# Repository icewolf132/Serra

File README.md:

<div align="center">

# Serra automatizzata

### Sistema embedded per il controllo di una serra con microcontrollori Microchip PIC

*Un progetto pratico che integra firmware per microcontrollori, progettazione elettronica e controllo di sensori e attuatori.*

</div>

---

## Panoramica

Questa **serra automatizzata** è un progetto embedded sviluppato per riprodurre, su scala prototipale, alcuni elementi di un sistema di controllo per una serra industriale. Il sistema combina due microcontrollori **Microchip PIC16F887 e PIC16F88**, schede elettroniche progettate e realizzate appositamente, sensori di temperatura e attuatori per la ventilazione e il movimento dell'asta d'irrigazione.

Il progetto comprende sia la parte software — firmware dei microcontrollori — sia la parte hardware: schemi elettrici, progettazione delle PCB e integrazione dei componenti. Il repository raccoglie il materiale tecnico disponibile e offre una base per documentare il funzionamento del sistema e le successive evoluzioni.

> **Stato del progetto:** il sistema di base è stato realizzato. È in progetto un'evoluzione con funzionalità IoT e soluzioni di comunicazione più strutturate. Le funzionalità future sono indicate come tali e non come già implementate.

## Galleria del progetto

> **Aggiungi le fotografie reali del progetto** nella cartella `documentazione/immagini/`, usando i nomi indicati qui sotto. Le immagini verranno visualizzate direttamente nella pagina GitHub. Sono particolarmente utili una foto della serra completa, una foto per ciascuna PCB e un'immagine del layout in KiCad.

<div align="center">
  
  <p><em>Vista complessiva del prototipo</em></p>
</div>

<table>
  <tr>
    <td width="50%" align="center">
      
      <br/><em>Panello di controllo</em>
    </td>
    <td width="50%" align="center">
      
      <br/><em>Scheda per il controllo del motore</em>
    </td>
  </tr>
  <tr>
    <td colspan="2" align="center">
      
      <br/><em>Progettazione elettronica in KiCad</em>
    </td>
  </tr>
</table>

## Funzionalità e componenti

Il prototipo comprende i seguenti elementi, realizzati o integrati nel sistema:

| Sistema | Componenti |
|---|---|
| Panello di controllo | Microcontrollore Microchip **PIC16F887** |
| Driver motore |  **PIC16F88** e  il ponte h **L298N** |
| Sensore di temperatura | Sensore analogico **LM35** |
| Ventilazione | Ventola comandata dal panello di controllo|
| Apertura delle finestre | Relè utilizzati per comandare il meccanismo di apertura |
| Movimento della barra d'irrigazione | **Motore DC da 12V** con **Encoder**, gestito dal driver motore |
| Hardware custom | Schede **PCB** progettate e realizzate personalmente (compresa la fotoincincisione)|

I maggiori dettagli riguardo i sensori e degli altri componenti possono essere consultati negli schemi elettrici e nei datasheet presenti nel repository.

## Architettura del sistema

Il sistema adotta una struttura composta da un controllore principale e da una scheda periferica dedicata al motore. I due PIC non utilizzano un protocollo seriale standard per comunicare: lo scambio di comandi avviene tramite **semplici segnali digitali**, interpretati come livello logico alto o basso.

<div align="center">
  
</div>

*Il diagramma è una rappresentazione concettuale dell'architettura descritta. Per i collegamenti elettrici dettagliati fanno fede gli schemi del progetto.*

### Schede elettroniche e PCB

La parte hardware è stata progettata e realizzata nell'ambito del progetto, non assemblata esclusivamente usando moduli già pronti. Il repository include i materiali di progettazione elettronica sviluppati con **KiCad**.

La documentazione hardware è utile per:

- consultare gli schemi elettrici;
- esaminare il layout delle PCB;
- identificare i componenti e i relativi collegamenti;
- comprendere la separazione tra controllore principale e scheda periferica.

Quando possibile, è consigliato affiancare ai file sorgente di KiCad anche esportazioni PDF degli schemi, immagini del layout e fotografie delle schede fisiche assemblate.

## Firmware

Il firmware è organizzato in base al ruolo dei due microcontrollori:

- **Controllore principale — PIC16F887:** gestisce la logica centrale del sistema e interagisce con i sensori e gli attuatori previsti dall'architettura.
- **Controllore periferico — PIC16F88:** è dedicato al controllo del motore DC da 12 V tramite il ponte h **L298N** e riceve comandi dal controllore principale tramite segnali digitali.

I sorgenti sono disponibili nella cartella [`firmware/`](firmware/). Le istruzioni di compilazione e programmazione devono fare riferimento ai file di progetto e alla toolchain effettivamente utilizzata per il firmware, nonché **MPLAB IDE v6.20**.

> **Nota sulla comunicazione:** il collegamento tra i due microcontrollori è realizzato tramite livelli logici digitali. Non è implementato, nella versione descritta, un protocollo come UART, SPI o I²C.

## Struttura del repository

```text
Serra/
├── README.md
├── Firmware/          # Sorgenti dei firmware
├── Schemi/            # Schemi elettrici e progetti PCB (KiCad)
└── Documentazione/    # Relazione tecnica, datasheet e materiali di supporto
```

Questa è la struttura logica del progetto: alcuni nomi o sottopercorsi possono variare in base all'organizzazione effettiva dei file nel repository.

## Documentazione tecnica

Nel repository sono raccolti diversi tipi di materiale tecnico:

- **Relazione tecnica PDF:** descrizione formale del progetto, delle scelte progettuali e dei problemi riscontrati. 
- **Schemi e PCB KiCad:** sorgenti editabili della progettazione elettronica.
- **Datasheet:** documentazione dei produttori per consultare caratteristiche elettriche, pinout, limiti operativi e modalità d'impiego dei componenti.
- **Firmware:** codice dei microcontrollori impiegati nel prototipo.

Per facilitare la consultazione, è consigliato mantenere i datasheet raggruppati in una cartella dedicata e creare un piccolo indice con **sigla del componente**, **funzione nel progetto** e **nome del relativo PDF**.

## Sviluppi futuri

Il progetto è in evoluzione. Le direzioni di sviluppo considerate comprendono:

- integrazione di funzionalità **IoT** per il monitoraggio del sistema;
- impiego di protocolli di comunicazione più strutturati per la raccolta e la gestione dei dati dei sensori;
- ampliamento della documentazione e miglioramento della diagnostica;

Questi punti rappresentano obiettivi di sviluppo e non vanno intesi come funzionalità già presenti nella versione attuale.

## Autore e contatti

Progetto sviluppato da **William Landolfi**.

- GitHub: [@icewolf132](https://github.com/icewolf132)
- Repository: [github.com/icewolf132/Serra](https://github.com/icewolf132/Serra)

---

<div align="center">
  <sub>Serra automatizzata · Progetto embedded, progettazione elettronica e controllo di attuatori</sub>
</div>

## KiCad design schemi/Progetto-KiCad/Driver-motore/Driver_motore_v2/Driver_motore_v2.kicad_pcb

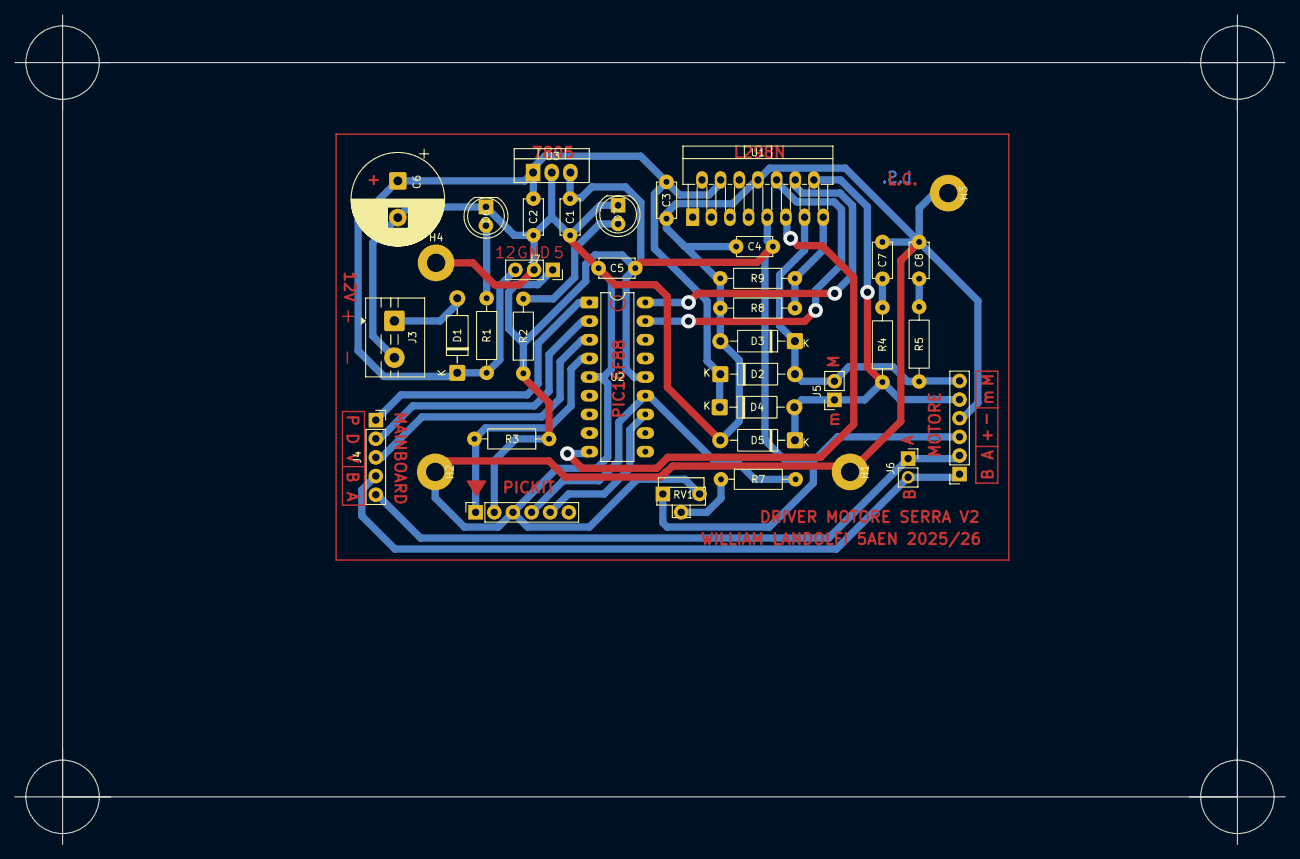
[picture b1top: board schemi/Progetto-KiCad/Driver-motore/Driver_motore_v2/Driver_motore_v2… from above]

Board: 2 copper layers, 172.9 x 112.9 mm, 38 parts (0 on the bottom side), 23 nets.

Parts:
C1, C3, C4, C5, C7, C8: 100nF; C_Disc_D4.7mm_W2.5mm_P5.00mm
C2: 220nF; C_Disc_D4.7mm_W2.5mm_P5.00mm
C6: 4.7m; CP_Radial_D12.5mm_P5.00mm
D1: 1N4007; D_DO-41_SOD81_P10.16mm_Horizontal
D2, D3, D4, D5: 1N5819; D_DO-41_SOD81_P10.16mm_Horizontal
D6, D7: LED; LED_D5.0mm
H1, H2, H3, H4: MountingHole_Pad; MountingHole_2.5mm_Pad
J1: PICKIT; PinSocket_1x06_P2.54mm_Vertical
J2: Motore; PinSocket_1x06_P2.54mm_Vertical
J3: Power; TerminalBlock_MaiXu_MX126-5.0-02P_1x02_P5.00mm
J4: Conn; PinSocket_1x05_P2.54mm_Vertical
J5: controllo_motore; PinSocket_1x02_P2.54mm_Vertical
J6: controllo_encoder; PinSocket_1x02_P2.54mm_Vertical
J7: controllo_alimentazione; PinSocket_1x03_P2.54mm_Vertical
R1, R2, R3, R4, R5: 10k; R_Axial_DIN0207_L6.3mm_D2.5mm_P10.16mm_Horizontal
R7: 220; R_Axial_DIN0207_L6.3mm_D2.5mm_P10.16mm_Horizontal
R8, R9: 1; R_Axial_DIN0207_L6.3mm_D2.5mm_P10.16mm_Horizontal
RV1: 10k; Potentiometer_Runtron_RM-063_Horizontal
U1: L298N; TO-220-15_P2.54x5.08mm_StaggerOdd_Lead4.58mm_Vertical
U2: PIC16F88-IP; DIP-18_W7.62mm_LongPads
U3: LM7805_TO220; TO-220-3_Vertical

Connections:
+12V: C2.1, C3.2, C6.1, D1.1 (K), D2.1 (K), D4.1 (K), J7.3, R1.1, U1.4 (Vs), U3.1 (VI)
A: U1.10 (IN3), U2.17 (AN0/RA0)
B: U1.12 (IN4), U2.18 (AN1/RA1)
C: U1.11 (EnB), U2.9 (RB3/PGM/CCP1)
Direzione: J4.2, U2.2 (C1OUT/Vref+/AN3/RA3)
Encoder A: J2.2, J4.5, J6.1
Encoder B: J2.1, J4.4, J6.2
Encoder GND: C1.1, C2.2, C3.1, C4.2, C5.1, C6.2, C7.2, C8.2, D3.2 (A), D5.2 (A), D6.1 (K), D7.1 (K), H1.1 (1_1), H2.1 (1_1), H3.1 (1_1), H4.1 (1_1), J1.3, J2.4, J3.2, J7.2, R8.2, R9.2, RV1.3, U1.8 (GND), U2.5 (VSS), U3.2 (GND)
Encoder Vcc: C1.2, C4.1, C5.2, J1.2, J2.3, J7.1, R2.1, R3.1, RV1.1, U1.9 (Vss), U2.14 (VDD), U3.3 (VO)
MLCR: J1.1, R3.2, U2.4 (~MCLR/Vpp/RA5)
Motor +: D2.2 (A), D3.1 (K), J2.6, J5.2, R5.1, U1.13 (OUT3)
Motor -: D4.2 (A), D5.1 (K), J2.5, J5.1, R4.1, U1.14 (OUT4)
unnamed: C7.1, R4.2
unnamed: C8.1, R5.2
unnamed: D1.2 (A), J3.1
unnamed: D6.2 (A), R1.2
unnamed: D7.2 (A), R2.2
unnamed: R7.1, RV1.2
unnamed: R8.1, R9.1, U1.15 (SENSE_B)
PGC: J1.5, U2.12 (RB6/AN5/PGC/T1CKI)
PGD: J1.4, R7.2, U2.13 (RB7/AN6/PGD/T1OSI)
Power: J4.1, U2.1 (Vref-/CVref/AN2/RA2)
Velocità: J4.3, U2.3 (C2OUT/T0CKI/AN4/RA4)

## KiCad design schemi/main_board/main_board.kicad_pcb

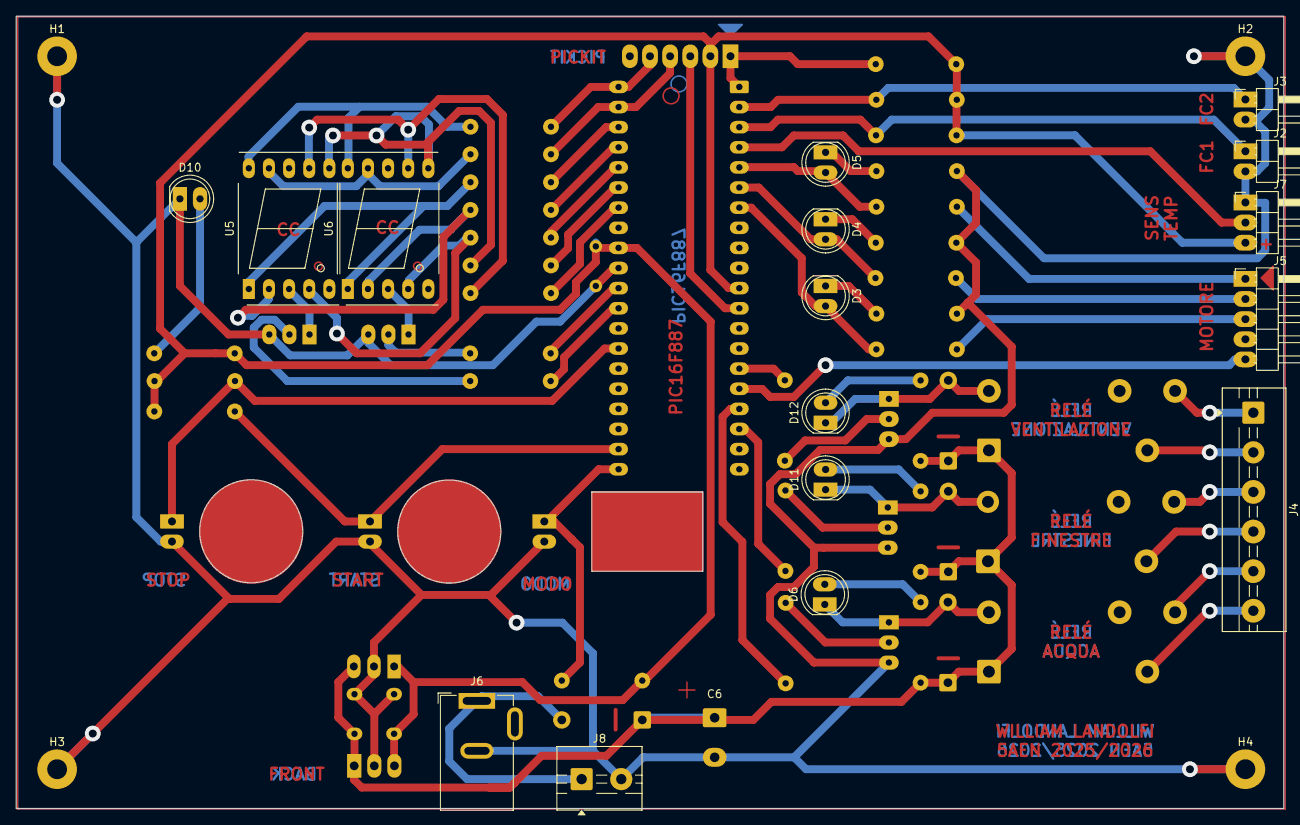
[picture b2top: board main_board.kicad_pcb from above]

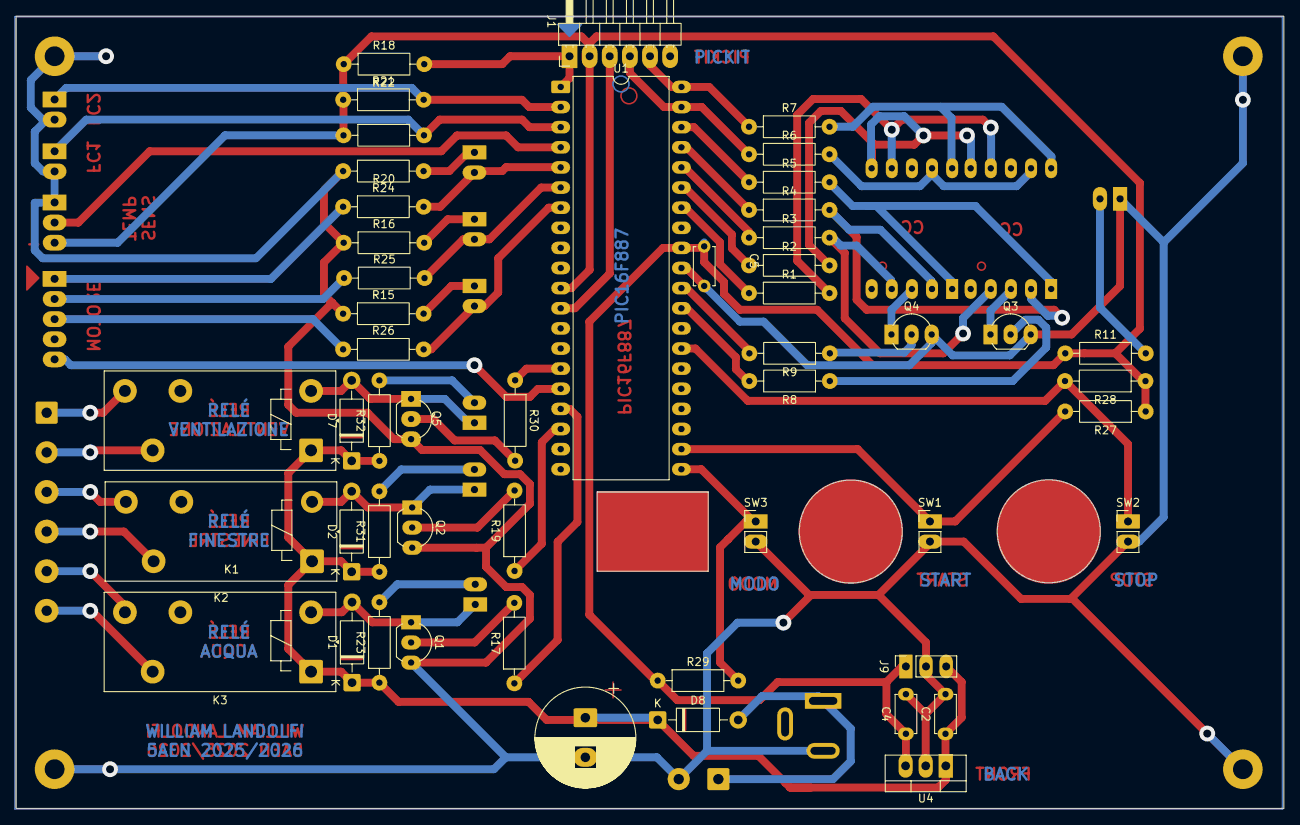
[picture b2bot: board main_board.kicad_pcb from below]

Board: 2 copper layers, 160.0 x 100.0 mm, 71 parts (51 on the bottom side), 60 nets.

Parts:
C2: 220nF; C_Disc_D4.7mm_W2.5mm_P5.00mm
C4, C5: 100nF; C_Disc_D4.7mm_W2.5mm_P5.00mm
C6: 4.7m; CP_Radial_D12.5mm_P5.00mm
D1, D2, D7: 1N4004; D_DO-41_SOD81_P10.16mm_Horizontal
D3, D4, D5, D6, D10, D11, D12: LED; LED_D5.0mm
D8: 1N4007; D_DO-41_SOD81_P10.16mm_Horizontal
H1, H2, H3, H4: MountingHole_Pad; MountingHole_2.5mm_Pad
J1: PICKIT; PinHeader_1x06_P2.54mm_Horizontal
J2: FC1; PinHeader_1x02_P2.54mm_Horizontal
J3: FC2; PinHeader_1x02_P2.54mm_Horizontal
J4: Conn_Relè; TerminalBlock_MaiXu_MX126-5.0-06P_1x06_P5.00mm
J5: MOTORE; PinHeader_1x05_P2.54mm_Horizontal
J6: Power_barrel; BarrelJack_GCT_DCJ200-10-A_Horizontal
J7: sensore_temp; PinHeader_1x03_P2.54mm_Horizontal
J8: Power; TerminalBlock_MaiXu_MX126-5.0-02P_1x02_P5.00mm
J9: controllo_alimentazione; PinSocket_1x03_P2.54mm_Vertical
K1: Ventilazione; Relay_SPDT_Finder_40.41
K2: finestre; Relay_SPDT_Finder_40.41
K3: acqua; Relay_SPDT_Finder_40.41
Q1, Q2, Q3, Q4, Q5: 2N2222A; TO-92_Inline_Wide
R1, R2, R3, R4, R5, R6, R7, R15, R16, R22, R24, R25, R26: 220; R_Axial_DIN0207_L6.3mm_D2.5mm_P10.16mm_Horizontal
R8, R9, R11, R23, R31, R32: R; R_Axial_DIN0207_L6.3mm_D2.5mm_P10.16mm_Horizontal
R17, R19, R30: 1K; R_Axial_DIN0207_L6.3mm_D2.5mm_P10.16mm_Horizontal
R18: 10k; R_Axial_DIN0207_L6.3mm_D2.5mm_P10.16mm_Horizontal
R20, R21, R27, R28, R29: 10K; R_Axial_DIN0207_L6.3mm_D2.5mm_P10.16mm_Horizontal
SW1: START; PinHeader_1x02_P2.54mm_Vertical
SW2: STOP; PinHeader_1x02_P2.54mm_Vertical
SW3: MODO; PinHeader_1x02_P2.54mm_Vertical
U1: PIC16F887-IP; DIP-40_W15.24mm_LongPads
U4: LM7805_TO220; TO-220-3_Vertical
U5, U6: SM420561N; 7SegmentLED_LTS6760_LTS6780

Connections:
+5V: C4.1, C5.1, J1.2, J7.3, J9.1, R11.1, R18.1, R20.1, R21.1, R27.1, R28.1, U1.11 (VDD), U1.32 (VDD), U4.3 (VO)
+12V: C2.1, C6.1, D1.1 (K), D2.1 (K), D7.1 (K), D8.1 (K), J9.3, K1.A1, K2.A1, K3.A1, R23.1, R31.1, R32.1, U4.1 (VI)
ACQUA: R17.1, U1.17 (P1A/CCP1/RC2)
DA: R1.1, U1.34 (C12IN3-/AN10/RB1)
DB: R2.1, U1.35 (AN8/RB2)
DC: R3.1, U1.36 (C12IN2-/PGM/AN9/RB3)
DD: R4.1, U1.37 (AN11/RB4)
DE: R5.1, U1.38 (~T1G/AN13/RB5)
DF: J1.4, R6.1, U1.39 (ICSPCLK/RB6)
DG: J1.5, R7.1, U1.40 (ICSPDAT/RB7)
Direzione: D4.2 (A), R25.2, U1.6 (C1OUT/T0CKI/RA4)
EN_D1: R8.2, U1.29 (RD6/P1C)
EN_D2: R9.2, U1.30 (RD7/P1D)
Encoder A: J5.5, U1.16 (T1OSI/CCP2/RC1)
FC1: J2.1, R20.2, U1.3 (C12IN1-/AN1/RA1)
FC2: J3.1, R21.2, U1.2 (C12IN0-/ULPWU/AN0/RA0)
FINESTRE: R19.1, U1.18 (SCL/SCK/RC3)
GND: C2.2, C4.2, C5.2, C6.2, D10.1 (K), H1.1 (1_1), H2.1 (1_1), H3.1 (1_1), H4.1 (1_1), J1.3, J2.2, J3.2, J6.2, J7.1, J8.2, J9.2, Q1.3 (E), Q2.3 (E), Q3.3 (E), Q4.3 (E), Q5.3 (E), R15.1, R16.1, R22.1, SW1.2, SW2.2, SW3.2 (B), U1.12 (VSS), U1.31 (VSS), U4.2 (GND)
MLCR: J1.1, R18.2, U1.1 (RE3/~MCLR/Vpp)
MODO: R29.2, SW3.1 (A), U1.21 (RD2)
unnamed: D1.2 (A), D6.1 (K), K3.A2, Q1.1 (C)
unnamed: D3.1 (K), R15.2
unnamed: D4.1 (K), R16.2
unnamed: D5.1 (K), R22.2
unnamed: D6.2 (A), R23.2
unnamed: D8.2 (A), J6.1, J8.1
unnamed: D10.2 (A), R11.2
unnamed: D11.2 (A), R31.2
unnamed: D2.2 (A), D11.1 (K), K2.A2, Q2.1 (C)
unnamed: D12.2 (A), R32.2
unnamed: D7.2 (A), D12.1 (K), K1.A2, Q5.1 (C)
unnamed: J5.1, R24.1
unnamed: J5.2, R25.1
unnamed: J5.3, R26.1
unnamed: Q1.2 (B), R17.2
unnamed: Q2.2 (B), R19.2
unnamed: Q3.2 (B), R8.1
unnamed: Q3.1 (C), U5.3 (CC), U5.8 (CC)
unnamed: Q4.2 (B), R9.1
unnamed: Q4.1 (C), U6.3 (CC), U6.8 (CC)
unnamed: Q5.2 (B), R30.2
unnamed: R1.2, U5.7 (A), U6.7 (A)
unnamed: R2.2, U5.6 (B), U6.6 (B)
unnamed: R3.2, U5.4 (C), U6.4 (C)
unnamed: R4.2, U5.2 (D), U6.2 (D)
unnamed: R5.2, U5.1 (E), U6.1 (E)
unnamed: R6.2, U5.9 (F), U6.9 (F)
unnamed: R7.2, U5.10 (G), U6.10 (G)
Power: D5.2 (A), R24.2, U1.5 (C1IN+/Vref+/AN3/RA3)
R1A: J4.1, K1.14
R1B: J4.2, K1.11
R2A: J4.3, K2.14
R2B: J4.4, K2.11
R3A: J4.5, K3.14
R3B: J4.6, K3.11
START: R27.2, SW1.1, U1.22 (RD3)
STOP: R28.2, SW2.1, U1.27 (RD4)
TEMP: J7.2, U1.4 (C2IN+/CVref/Vref-/AN2/RA2)
VENTILAZIONE: R30.1, U1.15 (T10S0/T1CKI/RC0)
Velocità: D3.2 (A), R26.2, U1.7 (C2OUT/~SS/AN4/RA5)

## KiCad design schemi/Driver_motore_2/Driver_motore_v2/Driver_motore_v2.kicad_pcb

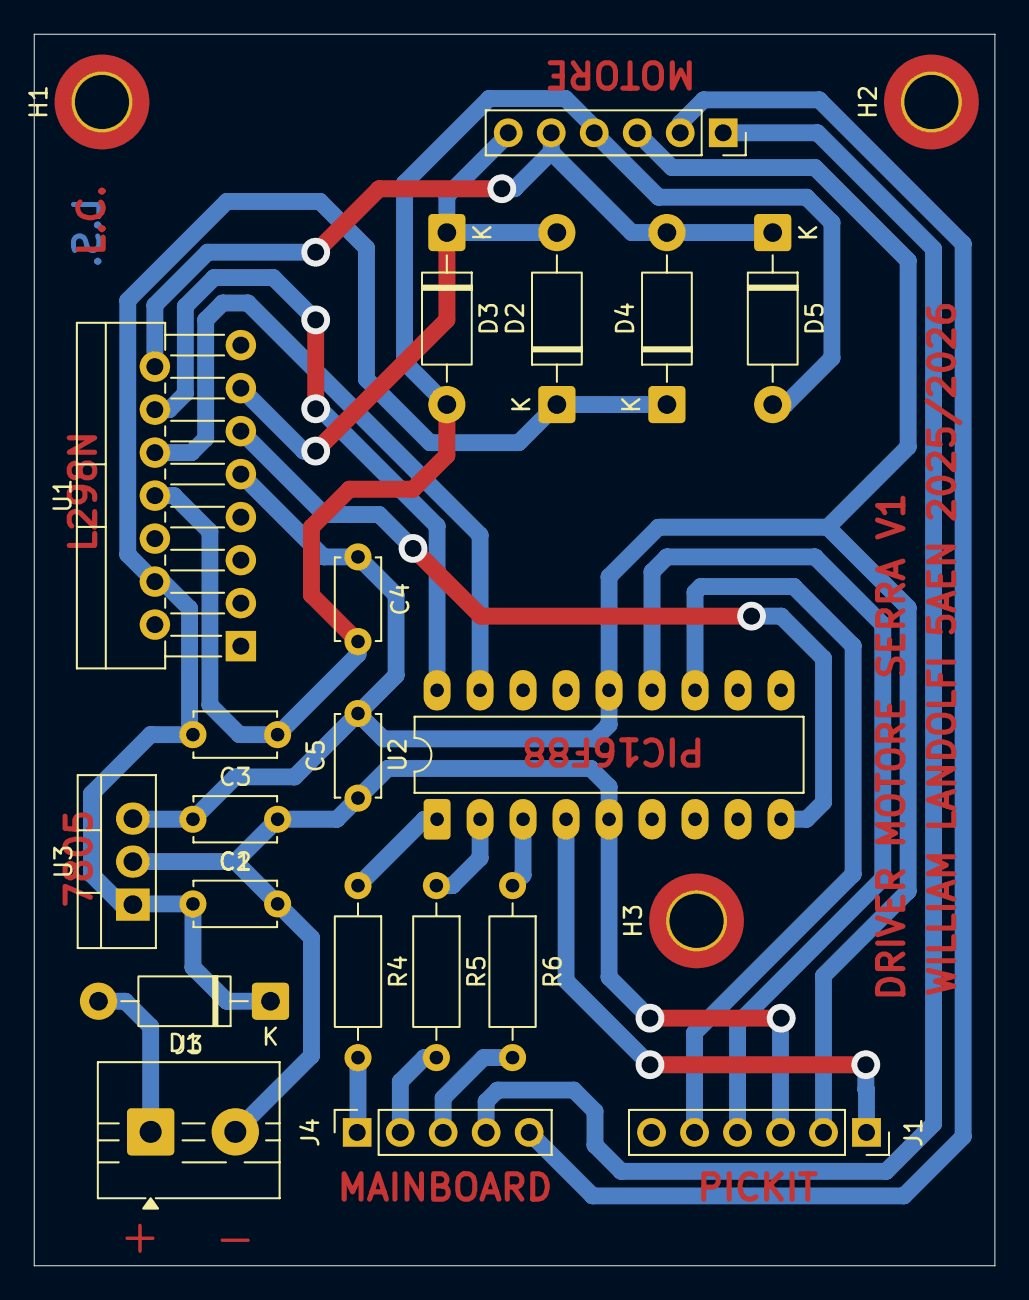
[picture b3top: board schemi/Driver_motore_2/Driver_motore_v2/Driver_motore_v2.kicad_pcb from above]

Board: 2 copper layers, 56.8 x 72.8 mm, 23 parts (0 on the bottom side), 20 nets.

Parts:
C1, C3, C4, C5: 100nF; C_Disc_D4.7mm_W2.5mm_P5.00mm
C2: 220nF; C_Disc_D4.7mm_W2.5mm_P5.00mm
D1: 1N4007; D_DO-41_SOD81_P10.16mm_Horizontal
D2, D3, D4, D5: 1N5819; D_DO-41_SOD81_P10.16mm_Horizontal
H1, H2, H3: MountingHole; MountingHole_3.2mm_M3_DIN965_Pad_TopBottom
J1: PICKIT; PinSocket_1x06_P2.54mm_Vertical
J2: Motore; PinSocket_1x06_P2.54mm_Vertical
J3: Power; TerminalBlock_MaiXu_MX126-5.0-02P_1x02_P5.00mm
J4: Conn; PinSocket_1x05_P2.54mm_Vertical
R4, R5, R6: 470; R_Axial_DIN0207_L6.3mm_D2.5mm_P10.16mm_Horizontal
U1: L298N; TO-220-15_P2.54x5.08mm_StaggerOdd_Lead4.58mm_Vertical
U2: PIC16F88-IP; DIP-18_W7.62mm_LongPads
U3: LM7805_TO220; TO-220-3_Vertical

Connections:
+12V: C2.1, C3.2, D1.1 (K), D2.1 (K), D4.1 (K), U1.4 (Vs), U3.1 (VI)
A: U1.10 (IN3), U2.17 (AN0/RA0)
B: U1.12 (IN4), U2.18 (AN1/RA1)
C: U1.11 (EnB), U2.9 (RB3/PGM/CCP1)
Direzione: J4.2, R5.2
Encoder A: J2.2, J4.5
Encoder B: J2.1, J4.4
Encoder GND: C1.1, C2.2, C3.1, C4.2, C5.1, D3.2 (A), D5.2 (A), J1.3, J2.4, J3.2, U1.8 (GND), U2.5 (VSS), U3.2 (GND)
Encoder Vcc: C1.2, C4.1, C5.2, J1.2, J2.3, U1.9 (Vss), U2.14 (VDD), U3.3 (VO)
MLCR: J1.1, U2.4 (~MCLR/Vpp/RA5)
Motor +: D2.2 (A), D3.1 (K), J2.6, U1.13 (OUT3)
Motor -: D4.2 (A), D5.1 (K), J2.5, U1.14 (OUT4)
unnamed: D1.2 (A), J3.1
unnamed: R5.1, U2.2 (C1OUT/Vref+/AN3/RA3)
unnamed: R6.1, U2.3 (C2OUT/T0CKI/AN4/RA4)
unnamed: R4.1, U2.1 (Vref-/CVref/AN2/RA2)
PGC: J1.5, U2.12 (RB6/AN5/PGC/T1CKI)
PGD: J1.4, U2.13 (RB7/AN6/PGD/T1OSI)
Power: J4.1, R4.2
Velocità: J4.3, R6.2

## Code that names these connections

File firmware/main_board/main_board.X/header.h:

// PIC16F887 Configuration Bit Settings

// 'C' source line config statements

// CONFIG1
#pragma config FOSC = INTRC_NOCLKOUT// Oscillator Selection bits (INTOSCIO oscillator: I/O function on RA6/OSC2/CLKOUT pin, I/O function on RA7/OSC1/CLKIN)
#pragma config WDTE = OFF       // Watchdog Timer Enable bit (WDT disabled and can be enabled by SWDTEN bit of the WDTCON register)
#pragma config PWRTE = ON       // Power-up Timer Enable bit (PWRT enabled)
#pragma config MCLRE = ON       // RE3/MCLR pin function select bit (RE3/MCLR pin function is MCLR)
#pragma config CP = OFF         // Code Protection bit (Program memory code protection is disabled)
#pragma config CPD = OFF        // Data Code Protection bit (Data memory code protection is disabled)
#pragma config BOREN = ON       // Brown Out Reset Selection bits (BOR enabled)
#pragma config IESO = OFF       // Internal External Switchover bit (Internal/External Switchover mode is disabled)
#pragma config FCMEN = OFF      // Fail-Safe Clock Monitor Enabled bit (Fail-Safe Clock Monitor is disabled)
#pragma config LVP = OFF        // Low Voltage Programming Enable bit (RB3 pin has digital I/O, HV on MCLR must be used for programming)

// CONFIG2
#pragma config BOR4V = BOR40V   // Brown-out Reset Selection bit (Brown-out Reset set to 4.0V)
#pragma config WRT = OFF        // Flash Program Memory Self Write Enable bits (Write protection off)

// #pragma config statements should precede project file includes.
// Use project enums instead of #define for ON and OFF.

#include <xc.h>

// Definizione del clock interno
#define _XTAL_FREQ 4000000  // 4MHz (modifica se cambi il clock)

//INPUT
#define FC1 RA1
#define FC2 RA0
#define TEMP RA2

//MOTORE
#define POWER RA3
#define DIREZIONE RA4
#define VELOCITA RA5
#define ENCODER RC1

//RELÈ
#define VENTILAZIONE RC0
#define ACQUA RC2
#define FINESTRE RC3

//TASTI
#define MODO RD2
#define START RD3
#define STOP RD4

//DISPLAY

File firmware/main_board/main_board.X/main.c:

/*
 * File:   main.c
 * Author: william
 *
 * Created on 17 maggio 2026, 18.39
 */

#include <xc.h>
#include "header.h"

// #################
// VARIABILI GLOBALI
// #################
int stato_mot = 0;
int stato_stop = 0;
int stato_start = 0;
int stop_flag = 0;

//assegno i caratteri
     int carattere_1[5] = 
    {
        0b01111110, // carattere O
        0b11100010, // carattere F
        0b10101000, // carattere n
        0b10110000, // carattere c
        0b11111000, // carattere E
    };

     int carattere_2[5] = 
    {
        0b01111110, // carattere O
        0b11100010, // carattere F
        0b10101000, // carattere n
        0b10110000, // carattere c
        0b11111000, // carattere E
    };

     int x, y;

volatile unsigned long ms = 0;
unsigned long start = 0;


// #################
// DRIVER
// #################
void driver( int Power, int Dir, int Vel, int Acqua)
{
    static int power, dir, vel,acqua;
    power = Power;
    dir = Dir;
    vel = Vel;
    acqua =Acqua;
            
    if (power == 0 )
        RA3 = 0;
    else if (power == 1)
        RA3 = 1;
    
    if (dir == 0 )
        RA4 = 0;
    else if (dir == 1)
        RA4 = 1;
    
    if (vel == 0 )
        RA5 = 0;
    else if (vel == 1)
        RA5 = 1;
    
    if (acqua == 0 )
        RC2 = 0;
    else if (acqua == 1)
        RC2 = 1;
}



// #################
// TIMER ISR (1ms tick)
// #################
void __interrupt() isr() 
{
    if (TMR1IF) {
        TMR1IF = 0;

        // preload per 1ms con Fosc=4MHz, prescaler 1:8
        TMR1 = 65411;

        ms++;
    }
}

// #################
// TASK MOTORE
// #################

void Task_Motore(void)
{
    if(stop_flag==0) 
    {
    switch(stato_mot)
    {
        case 0: // tutto spento
            driver(0,0,0,0);
            stato_start = 0;
            if(START == 0) stato_mot = 1; // se premo start
        break;

        case 1: // vedo dove sta la barra
            stato_start = 1;
            if(FC1 == 0) // se non sta all'inizio
                stato_mot = 2;
            else // se sta all'inizio
                stato_mot = 3;
        break;

        case 2: // torna indietro velocemente
            driver(1,0,1,0); 
            if(FC1 == 1) stato_mot = 3; // se arriva all'inizio
        break;

        case 3: // vai avanti irrigando
            driver(1,1,0,1);
            if(FC2 == 1) stato_mot = 4; // se sono arrivato alla fine
        break;

        case 4: // controllo il il modo del ritorno
            if(MODO == 1) stato_mot = 5; // se è impostato a 1 
            else stato_mot = 6; // se è impostato a 0
        break;

        case 5: // torno indietro irriganto
            driver(1,0,0,1);
            if(FC1 == 1) stato_mot = 0; // se arrivo all'inizio
        break;

        case 6: // torno indietro velocemente
            driver(1,0,1,0);
            if(FC1 == 1) 
            {   
                driver (1,1,1,0);
                __delay_ms(30);
                driver (0,0,0,0);
                stato_mot = 0; // se arrivo all'inizio
            }
        break;
        
    }
    }
}

// #################
// STOP 
// #################
void Task_Stop(void)
{
    switch(stato_stop)
    {
        case 0: //tasto non premuto aspetto che venga premuto
            if ((STOP == 0) && (stato_mot >> 1)) stato_stop = 1; // se il tasto viene premuto
        break;

        case 1: // il tasto è stato premuto
            stop_flag = 1; // segnalo che il tasto è stato premuto
            start = ms; // memorizzo a che ora è stato premuto il tasto
            driver(0,0,0,0); //fermo il motore
            stato_stop = 2;
        break;

        case 2:
            if (START == 0) // se dopodiche premo il tasto di start
                stato_stop = 3;
            else if (((ms - start) >= 5000) && STOP == 0) //se sono passati 5 secondi da quandoho premuto il tasto di stop ed il tasto è ancora premuto
                stato_stop = 4;
        break;

        case 3: // ho premuto il tasto di start
            stop_flag = 0; //segnalo che il programma può riprendere
            stato_stop = 0;
        break;

        case 4: // fai tornare la barra ad inizio serra
            stato_mot = 6; // dico al programma del motore da che punto deve continuare 
            stop_flag = 0; // segnalo che il motore può continuare il suo lavoro
            stato_stop = 5;
        break;
        
        case 5:
            if (stato_mot == 0 )stato_stop = 0;
        break;
    }
}

 
 
// #################
// VENTILAZIONE (Controllo Rel� Termostato)
// #################
void Task_Ventilazione(void)
{
    static unsigned int filtro = 0; 
    static char prima_lettura = 1;  
    unsigned int adc;

    // 1. IMPORTANTE: Aspetta che il condensatore dell'ADC si carichi
    __delay_us(20); 

    // 2. Fai partire la conversione
    GO_nDONE = 1;
    while(GO_nDONE); // Aspetta la fine
    
    adc = ((unsigned int)ADRESH << 8) | ADRESL;

    if(prima_lettura) {
        filtro = adc;
        prima_lettura = 0;
    } else {
        filtro = (filtro * 7 + adc) / 8; 
    }

    // Controllo soglie
    if(filtro >= 143)       // >= 70�C
    {
        VENTILAZIONE = 1;   
    }
    else if(filtro <= 72)   // <= 35�C
    {
        VENTILAZIONE = 0;   
    }
}

// #################
// VISUALIZZAZIONE
// #################
void Task_Visualizzazione (void)
{
    if (FC1 && FC2)
    {
        x = 1;     // F
        y = 3;     // c
    }
    else if (stop_flag)
    {
        x = 0;     // O
        y = 1;     // F
    }
    else if (stato_mot != 0)
    {
        x = 0;     // O
        y = 2;     // n
    }
    else
    {
        x = 0;     // O
        y = 0;     // O
    }

    // Visualizzo
        // digit 1 
    RD6 = 1;    //EN D1
    RD7 = 0;    //EN D2
    PORTB = carattere_1[x];
        // digit 2
    __delay_ms (5);
    RD6 = 0;    //EN D1
    RD7 = 1;    //EN D2
    PORTB = carattere_2[y];
    __delay_ms (5);
}

// #################
// INIT TIMER
// #################
void Timer1_Init(void)
{
    T1CON = 0b00110001;
    TMR1 = 65411;
    TMR1IE = 1;
    PEIE = 1;
    GIE = 1;
}

// #################
// MAIN
// #################
void main(void)
{
    // 1. Configurazione Oscillatore (4 MHz interno)
    OSCCON = 0b01100000;

    // 2. Configurazione I/O Direzione (TRIS)
    TRISA = 0b00000111;    // RA2 (AN2) deve essere ingresso
    TRISB = 0b00000000;
    TRISC = 0b00000010;    // Configura RC2 come uscita per il rel� (se usi RC2)
    TRISD = 0b00011100;

    // Stato iniziale delle uscite a zero
    PORTA = 0x00;
    PORTB = 0x00;
    PORTC = 0x00;
    PORTD = 0x00;

    // 3. Configurazione ADC per AN2
    ANSEL = 0x04;          // Imposta solo AN2 come analogico (0b00000100)
    ANSELH = 0x00;         // Tutti gli altri pin digitali

    ADCON1bits.ADFM = 1;   // Giustificazione a destra (importante per i 10 bit)
    ADCON1bits.VCFG0 = 0;  // Vref+ = VDD (5V)
    ADCON1bits.VCFG1 = 0;  // Vref- = VSS (GND)

    // ADCON0: bit7-6 (Fosc/8), bit5-2 (Channel AN2: 0010), bit1 (GO/DONE=0), bit0 (ADON=1)
    ADCON0 = 0b01001001;   

    // 4. Inizializzazione Periferiche e Interrupt
    Timer1_Init();

    while(1)
    {
        
        Task_Motore();
        Task_Stop();
        Task_Ventilazione();
        Task_Visualizzazione();
    }
}

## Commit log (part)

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2026-01-10 prova
2026-01-11 sistemato le logiche dei tasti
2026-01-12 sistemato il programma motore
2026-01-13 creato il programma d'irrigazione con implementazione motore
2026-01-13 boh sono 4 jic
2026-04-26 aggiundo il pcd del driver motore
2026-04-26 migliorato il main del driver motore
2026-04-27 sistemato le cartelle
2026-04-27 sistemato le funzione in main.c
2026-04-28 update main
2026-05-08 controllo errore RB3
2026-05-11 update schema e main
2026-05-18 creazione scheda main
2026-05-31 update main board
2026-06-01 aggiornamento stop e ventilazione aggiunta
2026-06-20 aggiunto la visualizzazione al panello di controllo
